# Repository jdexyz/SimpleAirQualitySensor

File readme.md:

# (A) Simple Air Quality Sensor

### Parts

All parts were bought from https://shop.pimoroni.com/

- [Adafruit MagTag - 2.9" Grayscale E-Ink WiFi Display](https://www.adafruit.com/product/4800)
- [Adafruit CCS811 Air Quality Sensor Breakout](https://www.adafruit.com/product/3566)
- [Adafruit PMSA003I Air Quality Breakout](https://www.adafruit.com/product/4632)
- [Adafruit SCD-41 - True CO2 Temperature and Humidity Sensor](https://www.adafruit.com/product/5190)
- [MICS6814 3-in-1 Gas Sensor Breakout (CO, NO2, NH3)](https://shop.pimoroni.com/products/mics6814-gas-sensor-breakout)
- [BME688 4-in-1 Air Quality Breakout](https://shop.pimoroni.com/products/bme688-breakout)
- [LiPo Battery Pack – 2000mAh](https://shop.pimoroni.com/products/lipo-battery-pack?variant=20429082247)

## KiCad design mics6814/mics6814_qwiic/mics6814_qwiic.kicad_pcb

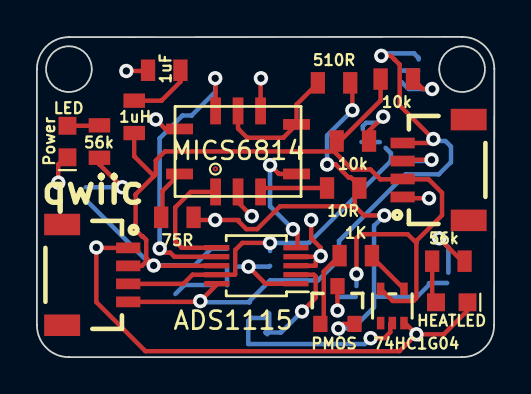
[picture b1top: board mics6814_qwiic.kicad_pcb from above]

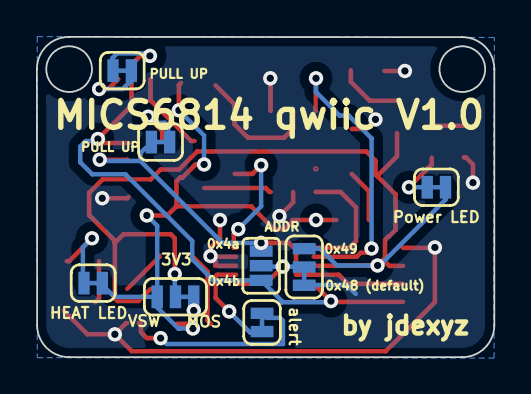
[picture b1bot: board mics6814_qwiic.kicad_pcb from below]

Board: 2 copper layers, 25.4 x 17.8 mm, 26 parts (8 on the bottom side), 24 nets.

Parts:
1uF: 1.0UF-0805-25V-10%; 0805
1uH: INDUCTOR-0805-3.3UH; 0805
ADS1115: ADS1115; MSOP-10_3x3mm_P0.5mm
D1: Power; LED-0603
D2: LED-RED1206; LED-0603
J1, J2: QWIIC_CONNECTORJS-1MM; 1X04_1MM_RA
JP1: ADDR1; SMT-JUMPER_3_1-NC_TRACE_SILK
JP2: Power LED; SMT-JUMPER_2_NC_TRACE_SILK
JP3: ADDR2; SMT-JUMPER_3_NO_SILK
JP4: HEAT LED; SMT-JUMPER_2_NC_TRACE_SILK
JP5: alert; SMT-JUMPER_2_NC_TRACE_SILK
JP6: VSW; SMT-JUMPER_3_1-NC_TRACE_SILK
JP7: PULL UP SDA; SMT-JUMPER_2_NC_TRACE_SILK
JP8: PULL UP SCL; SMT-JUMPER_2_NC_TRACE_SILK
MICS6814: MiCS-6814; MICS6814
Q1: MOSFET_PCH-DMG2307L; SOT23-3
R1, R6: 56k; 0805
R2: 510R; 0805
R3: 10R; 0805
R4: 75R; 0805
R5: 1K; 0805
R7, R8: 10k; 0805
U2: 74HC1G04; SOT353

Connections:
+3V3: 1uH.1, ADS1115.8 (VDD), J1.2 (VCC), J2.2 (VCC), JP1.1, JP2.2, JP6.2, R7.1, R8.1, U2.5 (P$V+)
+VSW: JP4.2, JP6.1, Q1.2 (S), R2.1, R3.2, R4.2
/ADDR: ADS1115.1 (ADDR), JP1.2, JP3.2
/ALERT: ADS1115.2 (ALERT/RDY), JP5.2
/CO_R: ADS1115.7 (AIN3), MICS6814.H
/NH3_R: ADS1115.5 (AIN1), MICS6814.D
/NO2_R: ADS1115.6 (AIN2), MICS6814.A
/SCL: ADS1115.10 (SCL), J1.4 (SCL), J2.4 (SCL), JP3.1, JP7.2
/SDA: ADS1115.9 (SDA), J1.3 (SDA), J2.3 (SDA), JP3.3, JP8.2
GND: 1uF.2, ADS1115.3 (GND), ADS1115.4 (AIN0), D1.C, D2.C, J1.1 (GND), J2.1 (GND), JP1.3, MICS6814.B, MICS6814.F, MICS6814.J, U2.3 (P$V-)
unnamed: D1.A, R1.1
unnamed: MICS6814.C, R3.1
unnamed: MICS6814.E, MICS6814.G, R2.2
unnamed: MICS6814.K, R4.1
unnamed: JP2.1, R1.2
unnamed: JP7.1, R7.2
unnamed: JP8.1, R8.2
unnamed: 1uF.1, 1uH.2
unnamed: Q1.1 (G), R5.2
unnamed: JP6.3, Q1.3 (D)
unnamed: R5.1, U2.4 (Y)
unnamed: D2.A, R6.1
unnamed: JP4.1, R6.2
unnamed: JP5.1, U2.2 (A)

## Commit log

2021-11-27 Add readme
2021-11-27 Add src
2021-11-28 Add more libraries
2021-11-28 Refactor
2021-12-12 Add fonts and lib
2021-12-12 Add voltage indicator
2022-02-02 WIP Add mics6814 support
2022-02-03 Add support for wake on button
2022-02-08 Add progress bar lib
2022-02-08 Make screen vertical
2022-02-08 Fix dev bugs
2022-02-09 Minor fix
2022-03-02 Update to auto detect sensors on start
2022-06-17 Add fonts
2022-06-17 Minor docs
2022-06-17 Add enclosure V1
2022-06-17 Update code
2022-06-17 update gitignore
2022-06-17 Better text
2022-06-22 Prettier text
2022-06-24 Add MICS6814 Qwiic board
2022-06-24 Board update
2022-06-24 Rounded corners
2022-06-24 Fix minor issues and MSSOP
2022-06-24 Add index to MICS6814
2022-06-24 Flex !
